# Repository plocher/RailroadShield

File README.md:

# RailroadShield
## License: CERN Open Hardware Licence v1.2

A community prototyping board to help with the bringup and maturation of OpenLCB.

Status: Prototypes fab'd and assembled, runs simple OpenLCB sketches, more testing underway in the OpenLCB community...

This project is an Arduino shield for Loconet, CAN and
[http://www.olcb.org/ OpenLCB] experimentation.  It is based on an
earlier set of experiments that only supported CAN and Loconet as
part of a custom 'duino stack which was used to build a [[ControlPoint]]
demo for the PCR Coast Division meet early in September, 2010.

I also spun solderless breadboard versions of the CANBusBreadboard
and LoconetBreadboard; the Loconet board works fine, but I have not
yet (2010) built and tested the CAN board.

The prototype served its purpose - it helped prove out the design
pattern of a local control point node that uses a local Loconet to
monitor occupancy detectors, turnouts and other "vital" logic as
well as control signals associated with the interlocking.  I built
a small handful of 8- and 16-bit I2C based I/O expander boards
(think mini-C/MRI) to make interfacing with control panels and LEDs
easier, but the power draw of 30 to 60 LEDs - even at 10mA ea - is
almost too much for the simple heatsinked 7805 linear regulator I
designed into the main board.  Better to use a distributed power
supply design, which means another design/fab cycle and more boards
in my junk drawer :-)

As in the real world, the control point passed Controls and Indications
back and forth along a code line; in the 1.0 demo, I used OPC_PEER_XFER
Loconet packets to emulate a code line; the next step is to use
CAN/openLCB instead.

The RailroadShield board is based on an expanded footprint Arduino
Shield template so that Decimila, Uno and Duemilanove boards can
easily be used with it.

This design has hardware support for

  * DCC  on D8,
  *  * See [http://www.nmra.org/standards/DCC/standards_rps/DCCStds.html NMRA DCC Standards] documentation
  * Loconet (RXD on D8, Lnet TXD on D7)
  *  * See Digitrax's [Loconet Personal Edition](http://www.digitrax.com/ftp/loconetpersonaledition.pdf)
  * CAN/openLCB using MCP2515 & MCP2551 on D13-D11,D9 & D3
  *  * See [OpenLCB info](http://openlcb.org/trunk/prototypes/Hobbyists.html)
  * RS485 full duplex/2 wire (NCE & XPressNet) or half duplex/4 wire (C/MRI) using the built in UART on D0/D1 with TX enable on D5
  *  * See Lenz's XpressNet: [Specification](http://www.lenz.com/manuals/xpressnet/xpressnet.pdf) and
  *  * NCE's cab bus [on page 32 of the Power Pro System Reference Manual](http://www.ncedcc.com/images/stories/manuals/sysman07.pdf)
  * 4 buttons+LEDs for simple I/O testing.

Let me know if you develop sketches or libraries for the above and
I will update this page with links.  Better yet, contribute the
code back to the openlcb.org openLCB project.

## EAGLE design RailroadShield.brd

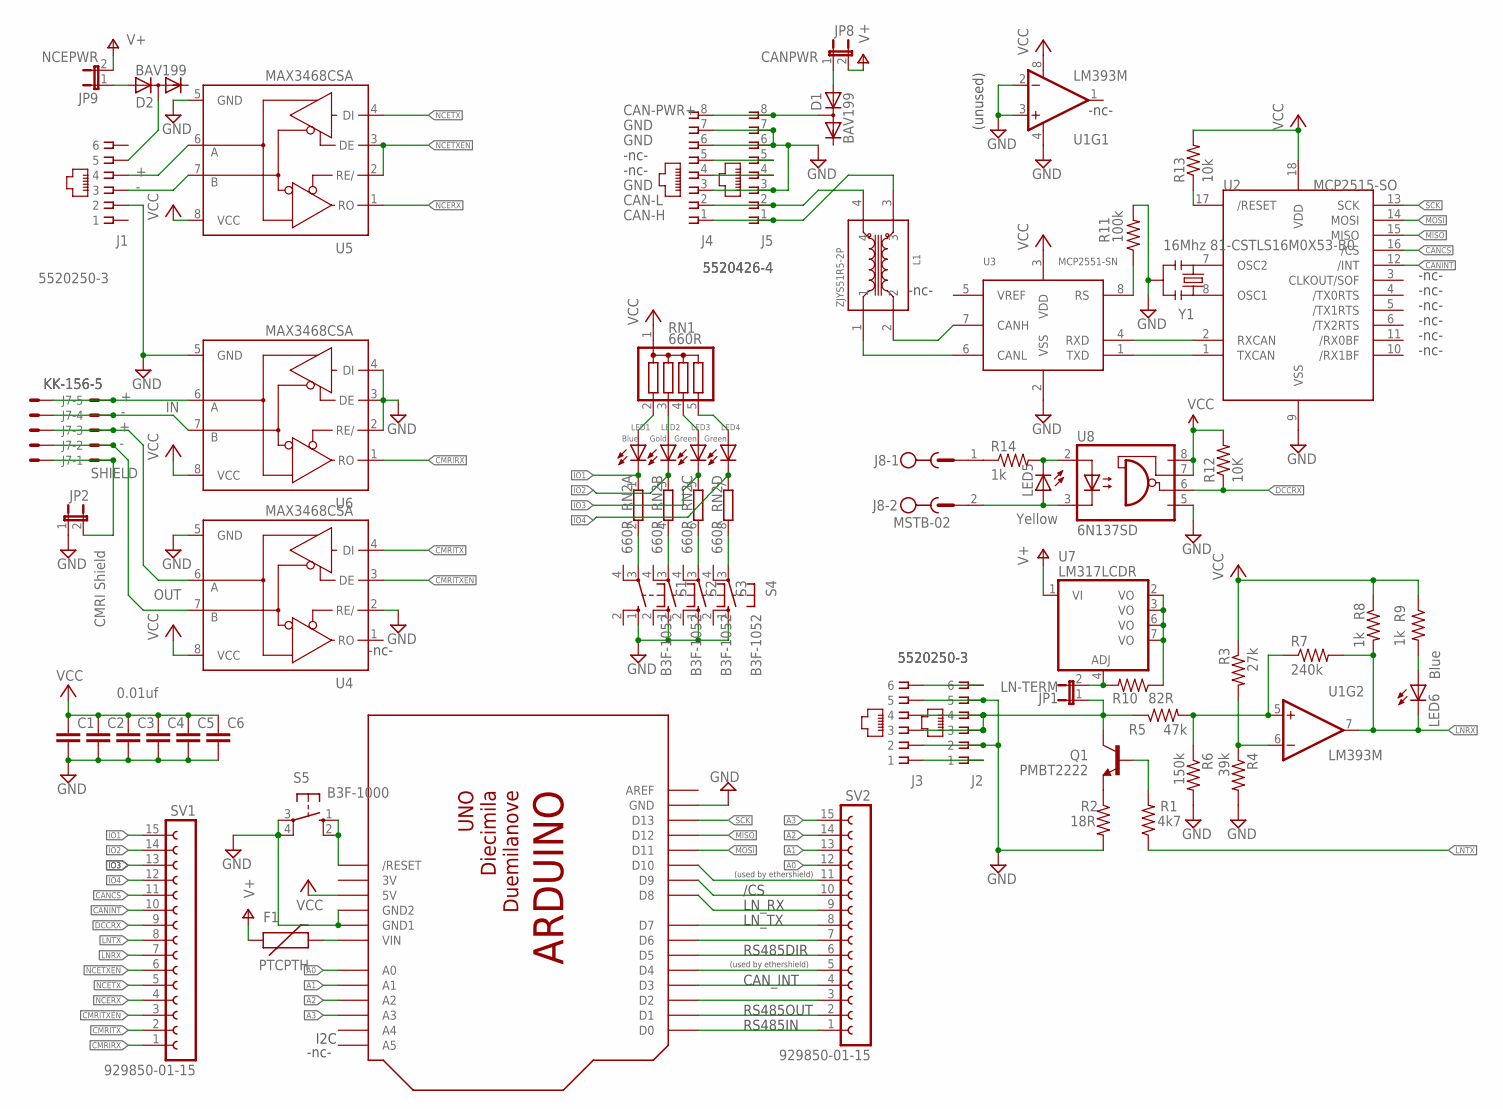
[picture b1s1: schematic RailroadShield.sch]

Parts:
C1, C2, C3, C4, C5, C6: 0.01uf; 0805
D1, D2: BAV199; SOT23
F1: PTCPTH; PTC
J1, J2, J3: 5520250-3; RJ11-NO_SHIELD
J4, J5: 5520426-4; RJ45-NO-SHIELD
J6, J7: KK-156-5
J8: MSTB-02; MSTBV2
JP1: LN-TERM; 1X02_LOCK
JP2: CMRI Shield; 1X02_LOCK
JP8: CANPWR; 1X02_LOCK
JP9: NCEPWR; 1X02_LOCK
L1: ZJYS51R5-2P; ZJYS
LED1, LED6: Blue; CHIP-LED0805
LED2: Gold; CHIP-LED0805
LED3, LED4: Green; CHIP-LED0805
LED5: Yellow; CHIP-LED0805
Q1: PMBT2222; SOT23-3
R1: 4k7; R0805
R2: 18R; R0805
R3: 27k; R0805
R4: 39k; R0805
R5: 47k; R0805
R6: 150k; R0805
R7: 240k; R0805
R8, R9, R14: 1k; R0805
R10: 82R; R0805
R11: 100k; R0805
R12: 10K; R0805
R13: 10k; R0805
RN1: 660R; SIL5
RN2: 660R; SIL8
S1, S2, S3, S4: B3F-1052; B3F-10XX
S5: B3F-1000; B3F-10XX
SV1, SV2: 929850-01-15; FE15
U1: LM393M; SO08
U2: MCP2515-SO; SO-18W
U3: MCP2551-SN; SO-08
U4, U5, U6: MAX3468CSA; SO08
U7: LM317LCDR; SO08
U8: 6N137SD; SM8
U$1: ARDUINODUEMILANOVE; ARDUINO-BIGSHIELD
Y1: 16Mhz 81-CSTLS16M0X53-B0; RESONATOR-PTH

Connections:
3V: U$1.3V
/RESET: R13.1, U2.17 (/RESET)
A0: SV2.12, U$1.A0
A1: SV2.13, U$1.A1
A2: SV2.14, U$1.A2
A3: SV2.15, U$1.A3
A/RESET: S5.1 (S), S5.2 (S1), U$1.RESET (/RESET)
CAN-H: J4.1, J5.1, L1.3
CAN-L: J4.2, J5.2, L1.4
CAN-PWR+: D1.3 (AC), J4.8, J5.8
CANCS: SV1.11, U2.16 (/CS)
CANH: L1.2, U3.7 (CANH)
CANINT: SV1.10, U2.12 (/INT)
CANL: L1.1, U3.6 (CANL)
CMRIRX: SV1.1, U6.1 (RO)
CMRITX: SV1.2, U4.4 (DI)
CMRITXEN: SV1.3, U4.3 (DE)
D0: SV2.1, U$1.D0
D1: SV2.2, U$1.D1
D2: SV2.3, U$1.D2
D3: SV2.4, U$1.D3
D4: SV2.5, U$1.D4
D5: SV2.6, U$1.D5
D6: SV2.7, U$1.D6
D7: SV2.8, U$1.D7
D8: SV2.9, U$1.D8
D9: SV2.10, U$1.D9
D10: SV2.11, U$1.D10
DCC-A: LED5.C, R14.2, U8.2 (A)
DCCB: J8.2, LED5.A, U8.3 (C)
DCCRX: R12.1, SV1.9, U8.6 (VO)
GND: C1.2, C2.2, C3.2, C4.2, C5.2, C6.2, J1.2, J2.2, J2.5, J3.2, J3.5, J4.3, J4.6, J4.7, J5.3, J5.6, J5.7, JP2.1, R2.2, R4.2, R6.2, R11.2, S1.1 (S), S2.1 (S), S3.1 (S), S4.1 (S), S5.3, S5.4 (P1), U1.2 (-IN), U1.3 (+IN), U1.4 (V-), U2.9 (VSS), U3.2 (VSS), U4.2 (RE/), U4.5 (GND), U5.5 (GND), U6.2 (RE/), U6.3 (DE), U6.4 (DI), U6.5 (GND), U8.5 (GND), U$1.GND, U$1.GND1, U$1.GND2, Y1.2
IO1: LED1.C, RN2.1, SV1.15
IO2: LED2.C, RN2.3 (1), SV1.14
IO3: LED3.C, RN2.5 (1), SV1.13
IO4: LED4.C, RN2.7 (1), SV1.12
L6+: LED6.A, R9.2
LN-TX: Q1.1 (B), R1.2
LNRX: LED6.C, R7.2, R8.2, SV1.7, U1.7 (OUT)
LNTX: R1.1, SV1.8
LOCONET: J2.3, J2.4, J3.3, J3.4, JP1.1, Q1.3 (C), R5.1
LOCONET-IN: R5.2, R6.1, R7.1, U1.5 (+IN)
MISO: U2.15 (MISO), U$1.D12
MOSI: U2.14 (MOSI), U$1.D11
unnamed: Q1.2 (E), R2.1
unnamed: LED1.A, RN1.2
unnamed: LED2.A, RN1.3
unnamed: LED3.A, RN1.4
unnamed: LED4.A, RN1.5
unnamed: J6.1, J7.1, JP2.2
unnamed: J6.2, J7.2, U4.7 (B)
unnamed: J6.3, J7.3, U4.6 (A)
unnamed: J6.4, J7.4, U6.7 (B)
unnamed: J6.5, J7.5, U6.6 (A)
unnamed: J8.1, R14.1
unnamed: U2.8 (OSC1), Y1.3
unnamed: U2.7 (OSC2), Y1.1
unnamed: D2.1 (A), JP9.1
unnamed: D1.1 (A), JP8.1
unnamed: RN2.2, S1.3
unnamed: RN2.4 (2), S2.3
unnamed: RN2.6 (2), S3.3
unnamed: RN2.8 (2), S4.3
unnamed: JP1.2, R10.2, U7.4 (ADJ)
unnamed: F1.P$2 (2), U$1.VIN
N-A: J1.4, U5.6 (A)
N-B: J1.3, U5.7 (B)
NCE-PWR+: D2.3 (AC), J1.5
NCERX: SV1.4, U5.1 (RO)
NCETX: SV1.5, U5.4 (DI)
NCETXEN: SV1.6, U5.2 (RE/), U5.3 (DE)
O-RESA: J4.4, J5.4
O-RESB: J4.5, J5.5
RAILSYNCA: J2.6, J3.6
RAILSYNCB: J2.1, J3.1
RS: R11.1, U3.8 (RS)
RXCAN: U2.2 (RXCAN), U3.4 (RXD)
SCK: U2.13 (SCK), U$1.D13
TXCAN: U2.1 (TXCAN), U3.1 (TXD)
V+: F1.P$1 (1), JP8.2, JP9.2, U7.1 (VI)
V-LNREF: R3.2, R4.1, U1.6 (-IN)
VCC: C1.1, C2.1, C3.1, C4.1, C5.1, C6.1, R3.1, R8.1, R9.1, R12.2, R13.2, RN1.1, U1.8 (V+), U2.18 (VDD), U3.3 (VDD), U4.8 (VCC), U5.8 (VCC), U6.8 (VCC), U8.7 (VE), U8.8 (VCC), U$1.5V
VOUT: R10.1, U7.2 (VO), U7.3 (VO), U7.6 (VO), U7.7 (VO)

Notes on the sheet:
-nc-
(unused)
/CS
LN_RX
LN_TX
CAN_INT
RS485IN
RS485OUT
RS485DIR
OUT
SHIELD
(used by ethershield)
I2C

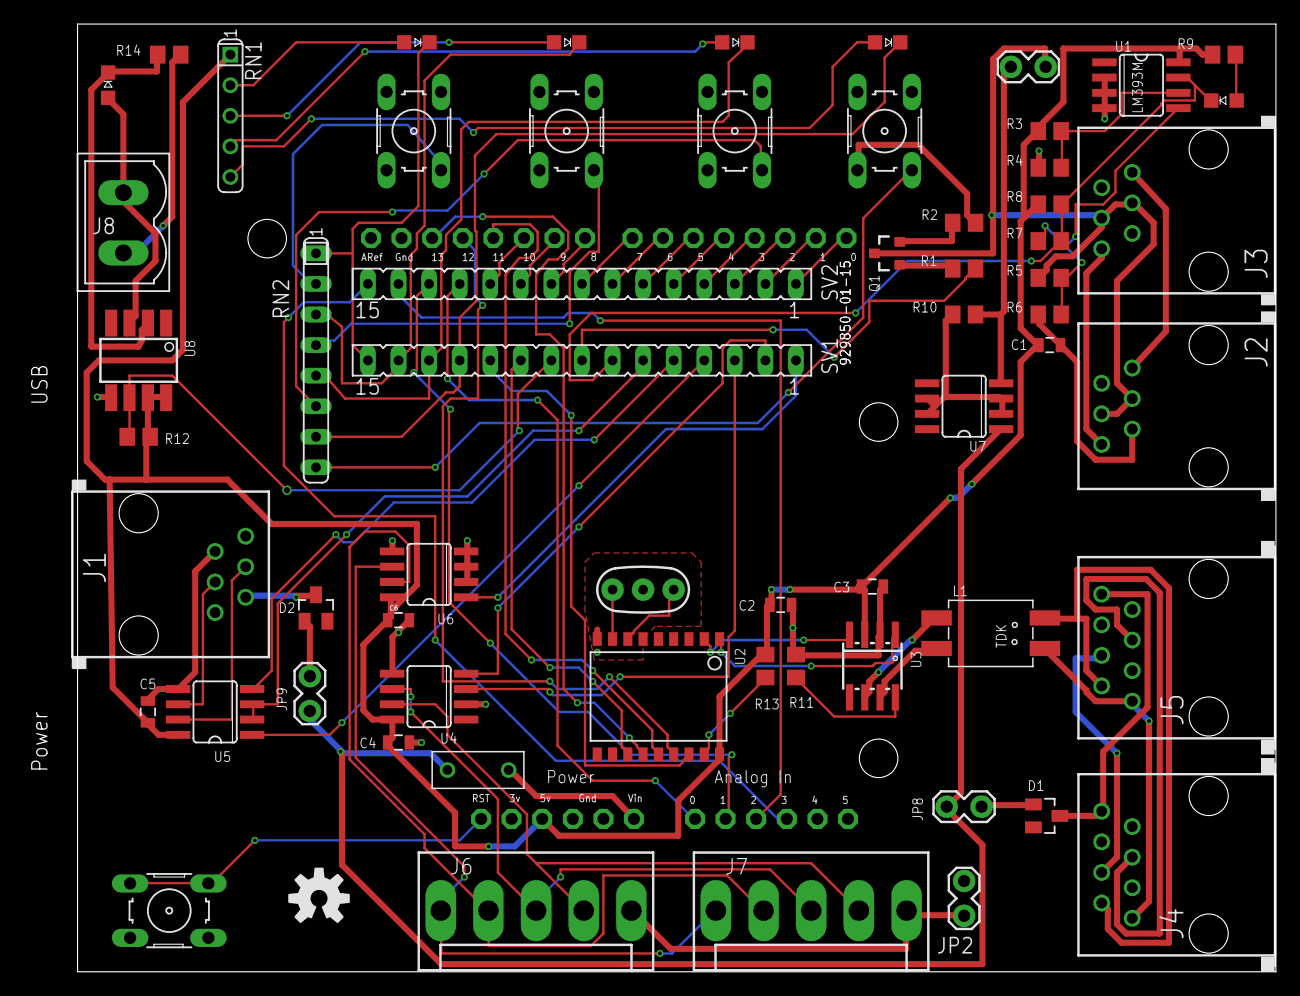
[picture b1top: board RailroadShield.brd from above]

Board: 2 copper layers, 104.0 x 78.7 mm, 63 parts (0 on the bottom side), 82 nets.

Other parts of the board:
U$2: OSHW-LOGOM; OSHW-LOGO-M

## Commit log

2019-11-26 2.1smd
2020-05-04 updated tags
2020-09-19 Obsolete
